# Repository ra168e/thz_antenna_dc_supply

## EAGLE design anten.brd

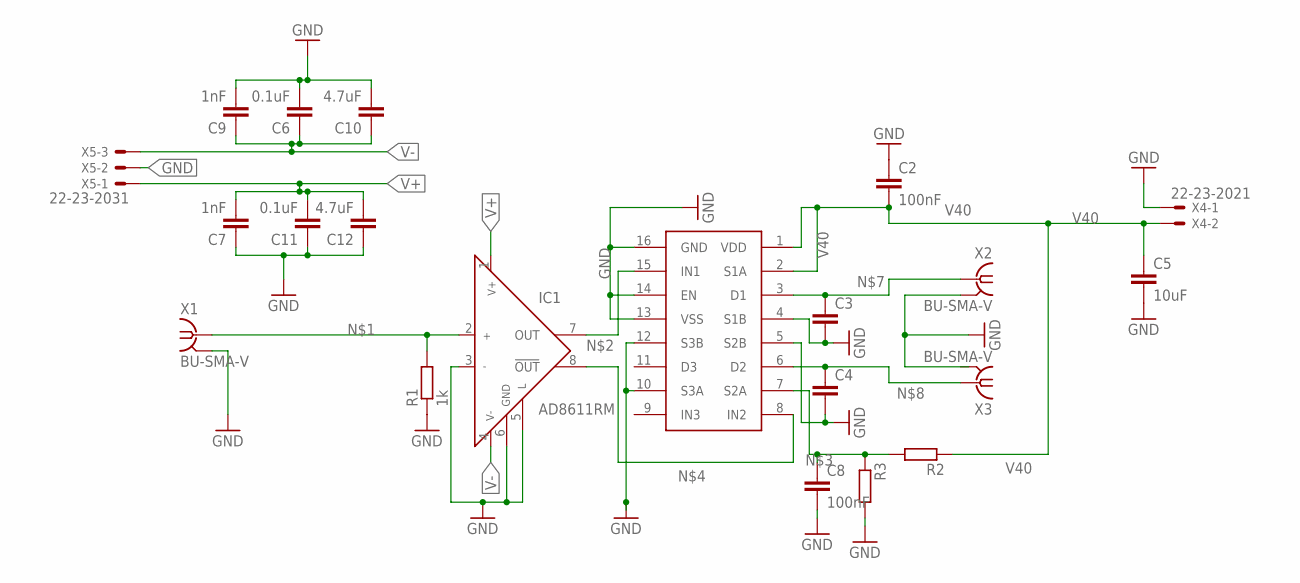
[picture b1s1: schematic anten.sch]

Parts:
C2, C8: 100nF; C0402
C3, C4: C-EUC0402; C0402
C5: 10uF; C1206
C6, C11: 0.1uF; C0805
C7, C9: 1nF; C0805
C10, C12: 4.7uF; C0805
IC1: AD8611RM; MSOP08
R1: 1k; R0402
R2, R3: R-EU_R0402; R0402
U$1: ADG5433; TSSOP16
X1, X2, X3: BU-SMA-V
X4: 22-23-2021
X5: 22-23-2031

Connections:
GND: C2.1, C3.2, C4.2, C5.2, C6.2, C7.1, C8.2, C9.2, C10.2, C11.1, C12.1, IC1.3 (IN-), IC1.5 (L), IC1.6 (GND), R1.1, R3.2, U$1.4 (S1B), U$1.5 (S2B), U$1.10 (S3A), U$1.12 (S3B), U$1.13 (VSS), U$1.14 (EN), U$1.16 (GND), X1.2, X1.3 (2), X1.4 (2), X1.5 (2), X2.2, X2.3 (2), X2.4 (2), X2.5 (2), X4.1, X5.2
unnamed: IC1.2 (IN+), R1.2, X1.1
unnamed: IC1.7 (OUT), U$1.15 (IN1)
unnamed: C8.1, R2.2, R3.1, U$1.7 (S2A)
unnamed: IC1.8 (!OUT), U$1.8 (IN2)
unnamed: C3.1, U$1.3 (D1), X2.1
unnamed: C4.1, U$1.6 (D2), X3.1
V40: C2.2, C5.1, R2.1, U$1.1 (VDD), U$1.2 (S1A), X4.2
V+: C7.2, C11.2, C12.2, IC1.1 (V+), X5.1
V-: C6.1, C9.1, C10.1, IC1.4 (V-), X5.3

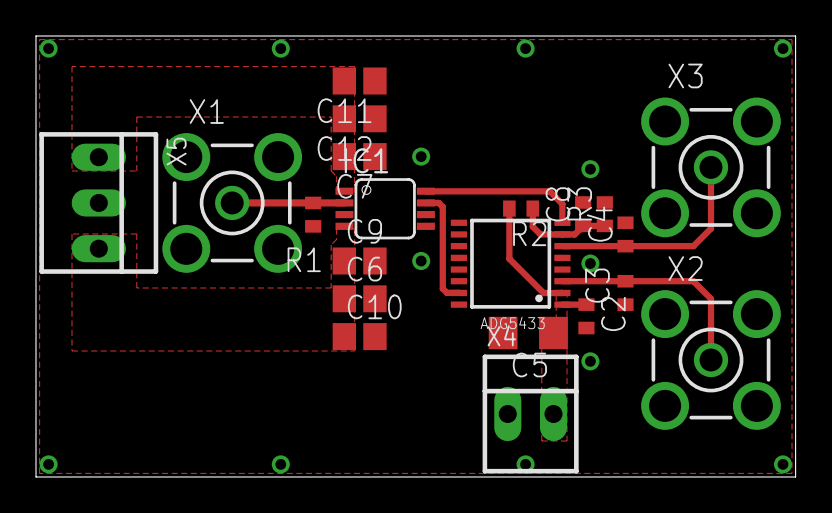
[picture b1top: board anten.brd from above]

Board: 2 copper layers, 42.2 x 24.5 mm, 21 parts (0 on the bottom side), 10 nets.

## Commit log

2017-03-03 Project Upload
2017-03-03 Changes to be committed: new file: Gerbers/anten.cmp new file: Gerbers/anten.dri new file: Gerbers/anten.gpi new file: Gerbers/anten.ncd new file: Gerbers/anten.sol new file: Gerbers/anten.stc new fi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
